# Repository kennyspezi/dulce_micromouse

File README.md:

# Dulce - Micromouse Robot (Fall-Spring 2024-25; Backlog)

A micromouse robot project designed for autonomous maze navigation with comprehensive sensing and motor control capabilities. I would like to revisit this when I get the chance!

## Overview

Dulce is a micromouse robot built around the Adafruit Itsy Bitsy SAMD21 3.3V microcontroller. The design features multiple infrared sensors for wall detection, a 9-axis IMU for orientation tracking, and dual DC motors with encoders for precise movement control.

## Gallery

### PCB Design

*Circuit schematic*

*PCB board layout*

### Hardware Build (before PCB design)

*Perfboard prototype - top view*

*Perfboard prototype - side view*

*Perfboard prototype - detailed view*

*Wiring connections*

*Soldering setup at IEEE station*

## Bill of Materials

| Component | Part Number/Model | Quantity | Description |
|-----------|------------------|----------|-------------|
| Microcontroller | Adafruit Itsy Bitsy SAMD21 3.3V | 1 | Main controller (SAMD21 ARM Cortex-M0+) |
| IR Reflective Sensors | 475-2649-ND | 7 | Wall detection and positioning |
| IMU | BNO-055 | 1 | 9-axis absolute orientation sensor |
| DC Motors with Encoders | - | 2 | Differential drive system |
| Motor Driver | DRV8833 | 1 | Dual H-bridge motor controller |
| Battery Connector | 2-pin connector | 1 | Main power supply |
| Misc. Connectors | 2-pin connectors | Various | Modular connections |

## Project Status

### Current Implementation
- ✅ Hardware schematic design (imported from EasyEDA)
- ✅ Pin definitions configured in firmware
- ✅ Basic Arduino framework setup with PlatformIO

### Future Work

#### Documentation Improvements
- My schematic-drafting skills have improved since I last touched this project. I would like to clean up my schematic exports.

#### Hardware Improvements
- **Sensor Optimization**: Evaluate whether fewer IR sensors can be used while maintaining diagonal movement capability
- **Mode Selection**: Add toggle button to switch between different operating modes
- **Status Indicator**: Integrate RGB LED to display current operational mode

#### Mechanical Design
- Design and CAD a custom chassis optimized for the electronic components
- Ensure proper sensor placement for accurate wall detection
- Optimize weight distribution and center of gravity

#### Software Development
- Implement multiple operational modes:
  - Object-following
  - IMU + PID "Compass" - inspired by [Haridev](https://github.com/haribood)
  - Wall-following algorithm
  - Maze solving
- Develop sensor calibration routines
- Implement PID control for motor control
- Add mode-switching logic with visual feedback

## Development Setup

### Prerequisites
- PlatformIO installed (via VS Code extension or CLI)
- USB cable for programming the Itsy Bitsy

### Building the Firmware
```bash
cd firmware
pio run
```

### Uploading to Device
```bash
pio run --target upload
```

## Pin Configuration

### IR Sensors
| Sensor Position | Pin |
|----------------|-----|
| Front Left | A1 |
| Front Center | A0 |
| Front Right | A2 |
| Mid Left | A3 |
| Mid Right | A4 |
| Back Left | A5 |
| Back Right | 0 (RX) |

### IMU (BNO-055)
| Function | Pin |
|----------|-----|
| Reset | D7 |
| Interrupt | D9 |

### Motor Control
| Motor | Pin A | Pin B |
|-------|-------|-------|
| Left Motor | 30 (SCK) | 29 (MOSI) |
| Right Motor | 28 (MISO) | 2 |

### Encoders
| Encoder | Channel A | Channel B |
|---------|-----------|----------|
| Left | D10 | D11 |
| Right | D12 | D13 |

See [firmware/src/main.cpp](firmware/src/main.cpp) for complete pin definitions.

## Project Structure
```
dulce/
├── electrical/          # KiCad PCB design files
│   ├── dulce_easyeda.kicad_sch
│   └── dulce_easyeda.kicad_pcb
├── firmware/           # Arduino/PlatformIO firmware
│   ├── src/
│   │   └── main.cpp
│   └── platformio.ini
└── README.md
```

## License

See [LICENSE](LICENSE) file for details.

## Contributing

This is a personal project :P

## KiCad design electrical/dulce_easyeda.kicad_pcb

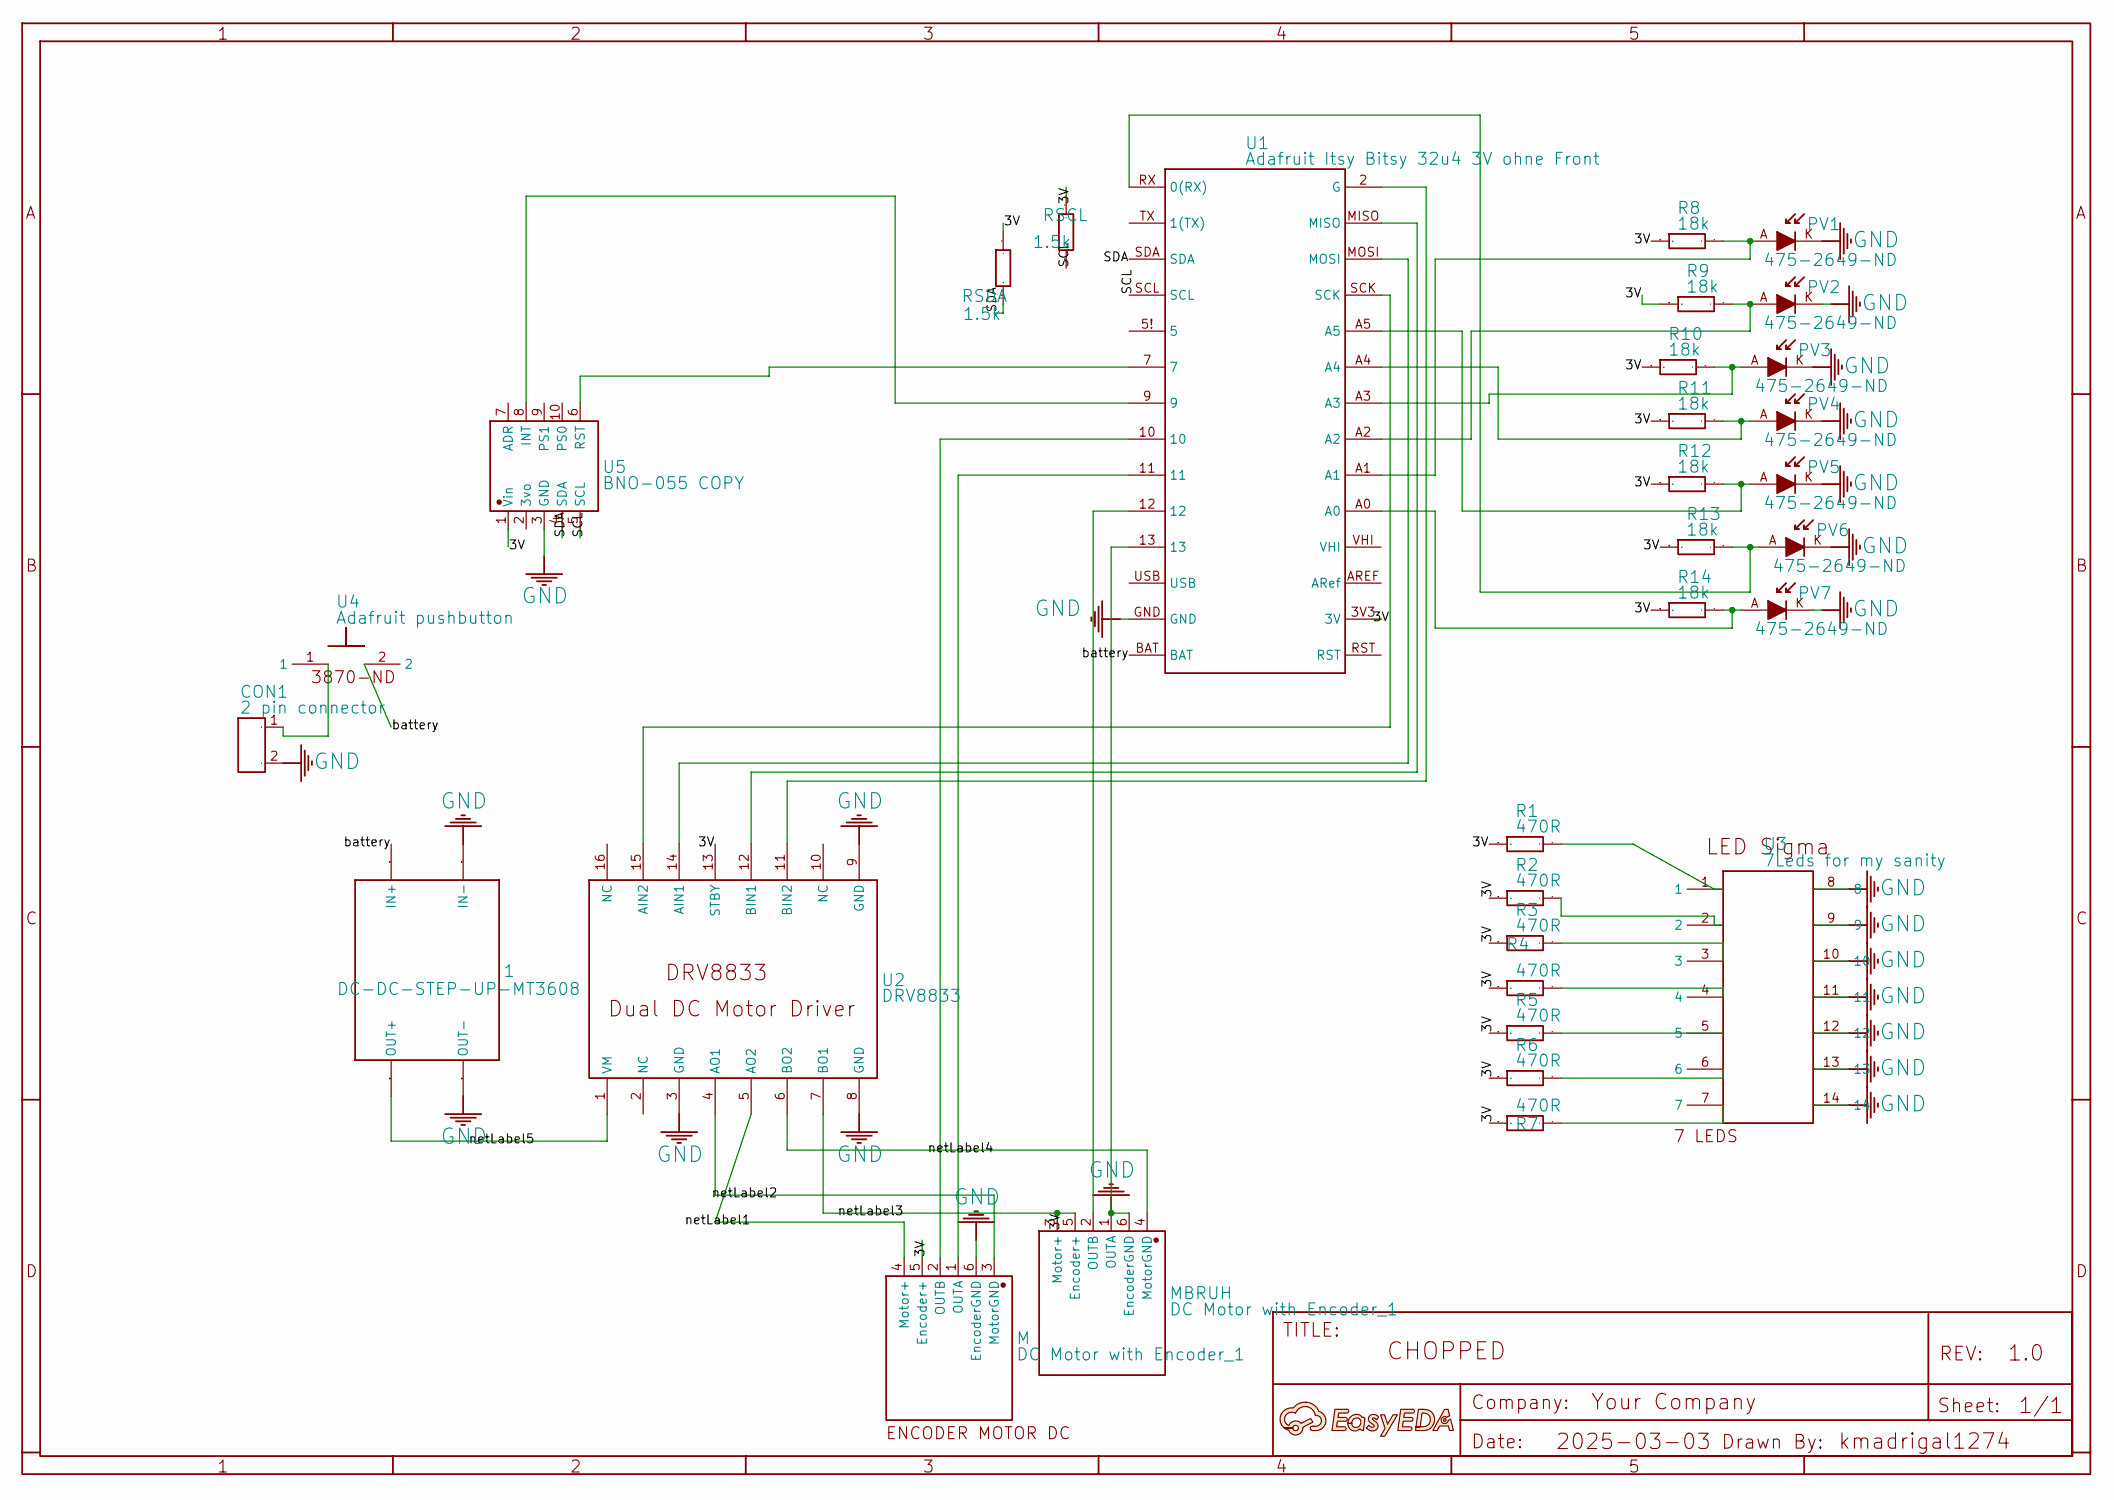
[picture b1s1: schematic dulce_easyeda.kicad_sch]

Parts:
1: DC-DC-STEP-UP-MT3608
A: A; Manufacturer Part ?
CON1: 2 pin connector
M: DC Motor with Encoder_1
MBRUH: DC Motor with Encoder_1
PV1, PV2, PV3, PV4, PV5, PV6, PV7: 475-2649-ND
R1, R2, R3, R4, R5, R6, R7: 470R; Manufacturer Part EWWR0001J20R0T9
R8, R9, R10, R11, R12, R13, R14: 18k; Manufacturer Part EWWR0001J20R0T9
RSCL: 1.5k; Manufacturer Part EWWR0001J20R0T9
RSDA: 1.5k; Manufacturer Part EWWR0001J20R0T9
U1: Adafruit Itsy Bitsy 32u4 3V ohne Front; Manufacturer Part Adafruit Itsy Bitsy 32u4 5V
U2: DRV8833
U3: 7Leds for my sanity
U4: Adafruit pushbutton
U5: BNO-055 COPY

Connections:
3V: M.5 (Encoder+), MBRUH.3 (Motor+), MBRUH.5 (Encoder+), R1.1, R2.1, R3.1, R4.1, R5.1, R6.1, R7.1, R8.1, R9.1, R10.1, R11.1, R12.1, R13.1, R14.1, RSCL.2, RSDA.2, U1.3V3 (3V), U2.7 (BO1), U2.13 (STBY), U5.1 (Vin)
BATTERY: 1.IN+, U1.BAT, U4.2
CON1_1: CON1.1, U4.1
NETLABEL1: M.4 (Motor+), U2.5 (AO2)
NETLABEL2: M.3 (MotorGND), U2.4 (AO1)
NETLABEL4: MBRUH.4 (MotorGND), U2.6 (BO2)
NETLABEL5: 1.OUT+, U2.1 (VM)
R1_2: R1.2, U3.1
R2_2: R2.2, U3.2
R3_2: R3.2, U3.3
R4_2: R4.2, U3.4
R5_2: R5.2, U3.5
R6_2: R6.2, U3.6
R7_2: R7.2, U3.7
SCL: RSCL.1, U1.SCL, U5.5 (SCL)
SDA: RSDA.1, U1.SDA, U5.4 (SDA)
U1_2: U1.2 (G), U2.11 (BIN2)
U1_5!: U1.5! (5)
U1_7: U1.7, U5.6 (RST)
U1_9: U1.9, U5.8 (INT)
U1_10: M.2 (OUTB), U1.10
U1_11: M.1 (OUTA), U1.11
U1_12: MBRUH.2 (OUTB), U1.12
U1_A0: PV7.A, R14.2, U1.A0
U1_A1: PV1.A, R8.2, U1.A1
U1_A2: PV2.A, R9.2, U1.A2
U1_A3: PV3.A, R10.2, U1.A3
U1_A4: PV4.A, R11.2, U1.A4
U1_A5: PV5.A, R12.2, U1.A5
U1_AREF: U1.AREF (ARef)
U1_MISO: U1.MISO, U2.12 (BIN1)
U1_MOSI: U1.MOSI, U2.14 (AIN1)
U1_RST: U1.RST
U1_RX: PV6.A, R13.2, U1.RX (0(RX))
U1_SCK: U1.SCK, U2.15 (AIN2)
U1_TX: U1.TX (1(TX))
U1_USB: U1.USB
U1_VHI: U1.VHI
U2_2: U2.2 (NC)
U2_10: U2.10 (NC)
U2_16: U2.16 (NC)
U5_2: U5.2 (3vo)
U5_7: U5.7 (ADR)
U5_9: U5.9 (PS1)
U5_10: U5.10 (PS0)

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
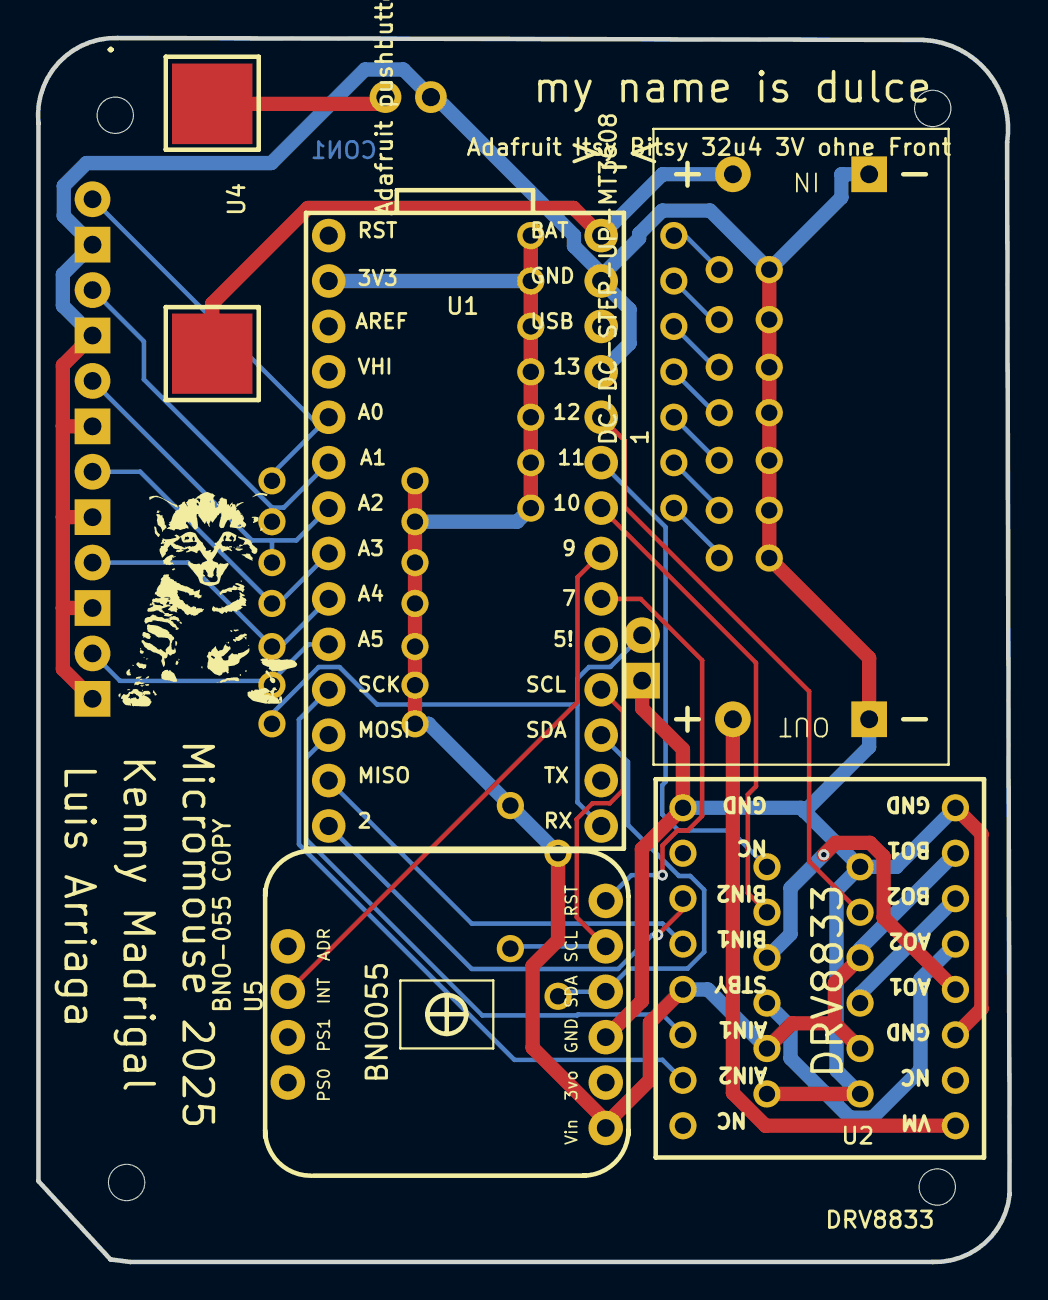
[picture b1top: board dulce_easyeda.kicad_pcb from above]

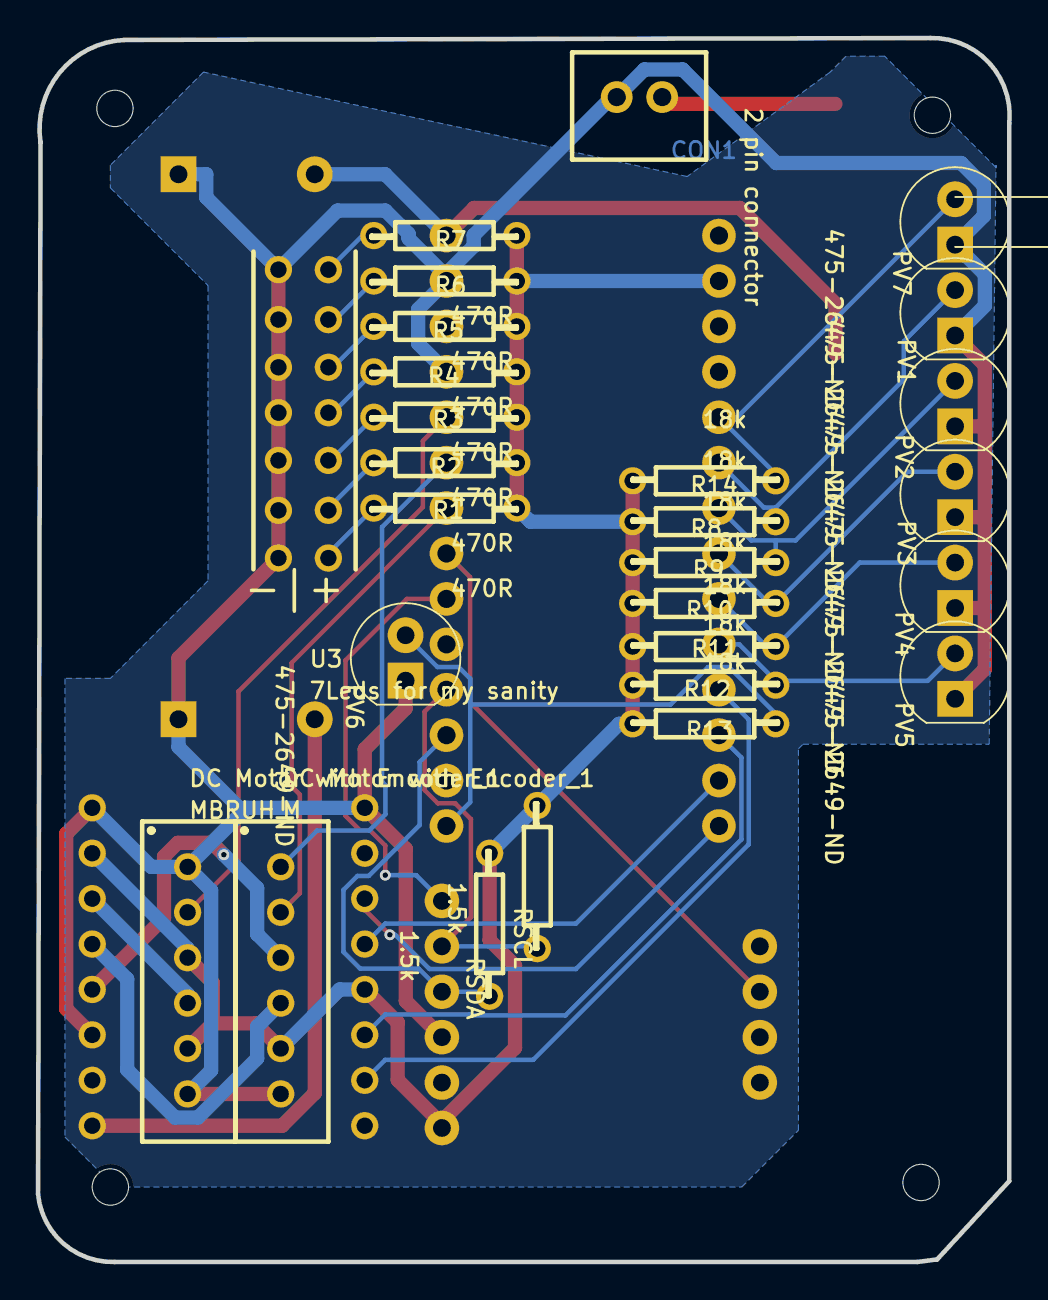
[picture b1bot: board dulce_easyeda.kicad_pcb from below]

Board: 2 copper layers, 54.3 x 68.5 mm, 36 parts (27 on the bottom side), 33 nets.

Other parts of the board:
Hole_gge4739: Hole_gge4739
Hole_gge4769: Hole_gge4769
Hole_gge4784: Hole_gge4784
Hole_gge4799: Hole_gge4799

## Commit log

2025-12-26 Easyeda files and gitignore
2025-12-26 EasyEDA to KiCad and Documentation.
